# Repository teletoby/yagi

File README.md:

# yagi
Yet Another Geiger Instrument

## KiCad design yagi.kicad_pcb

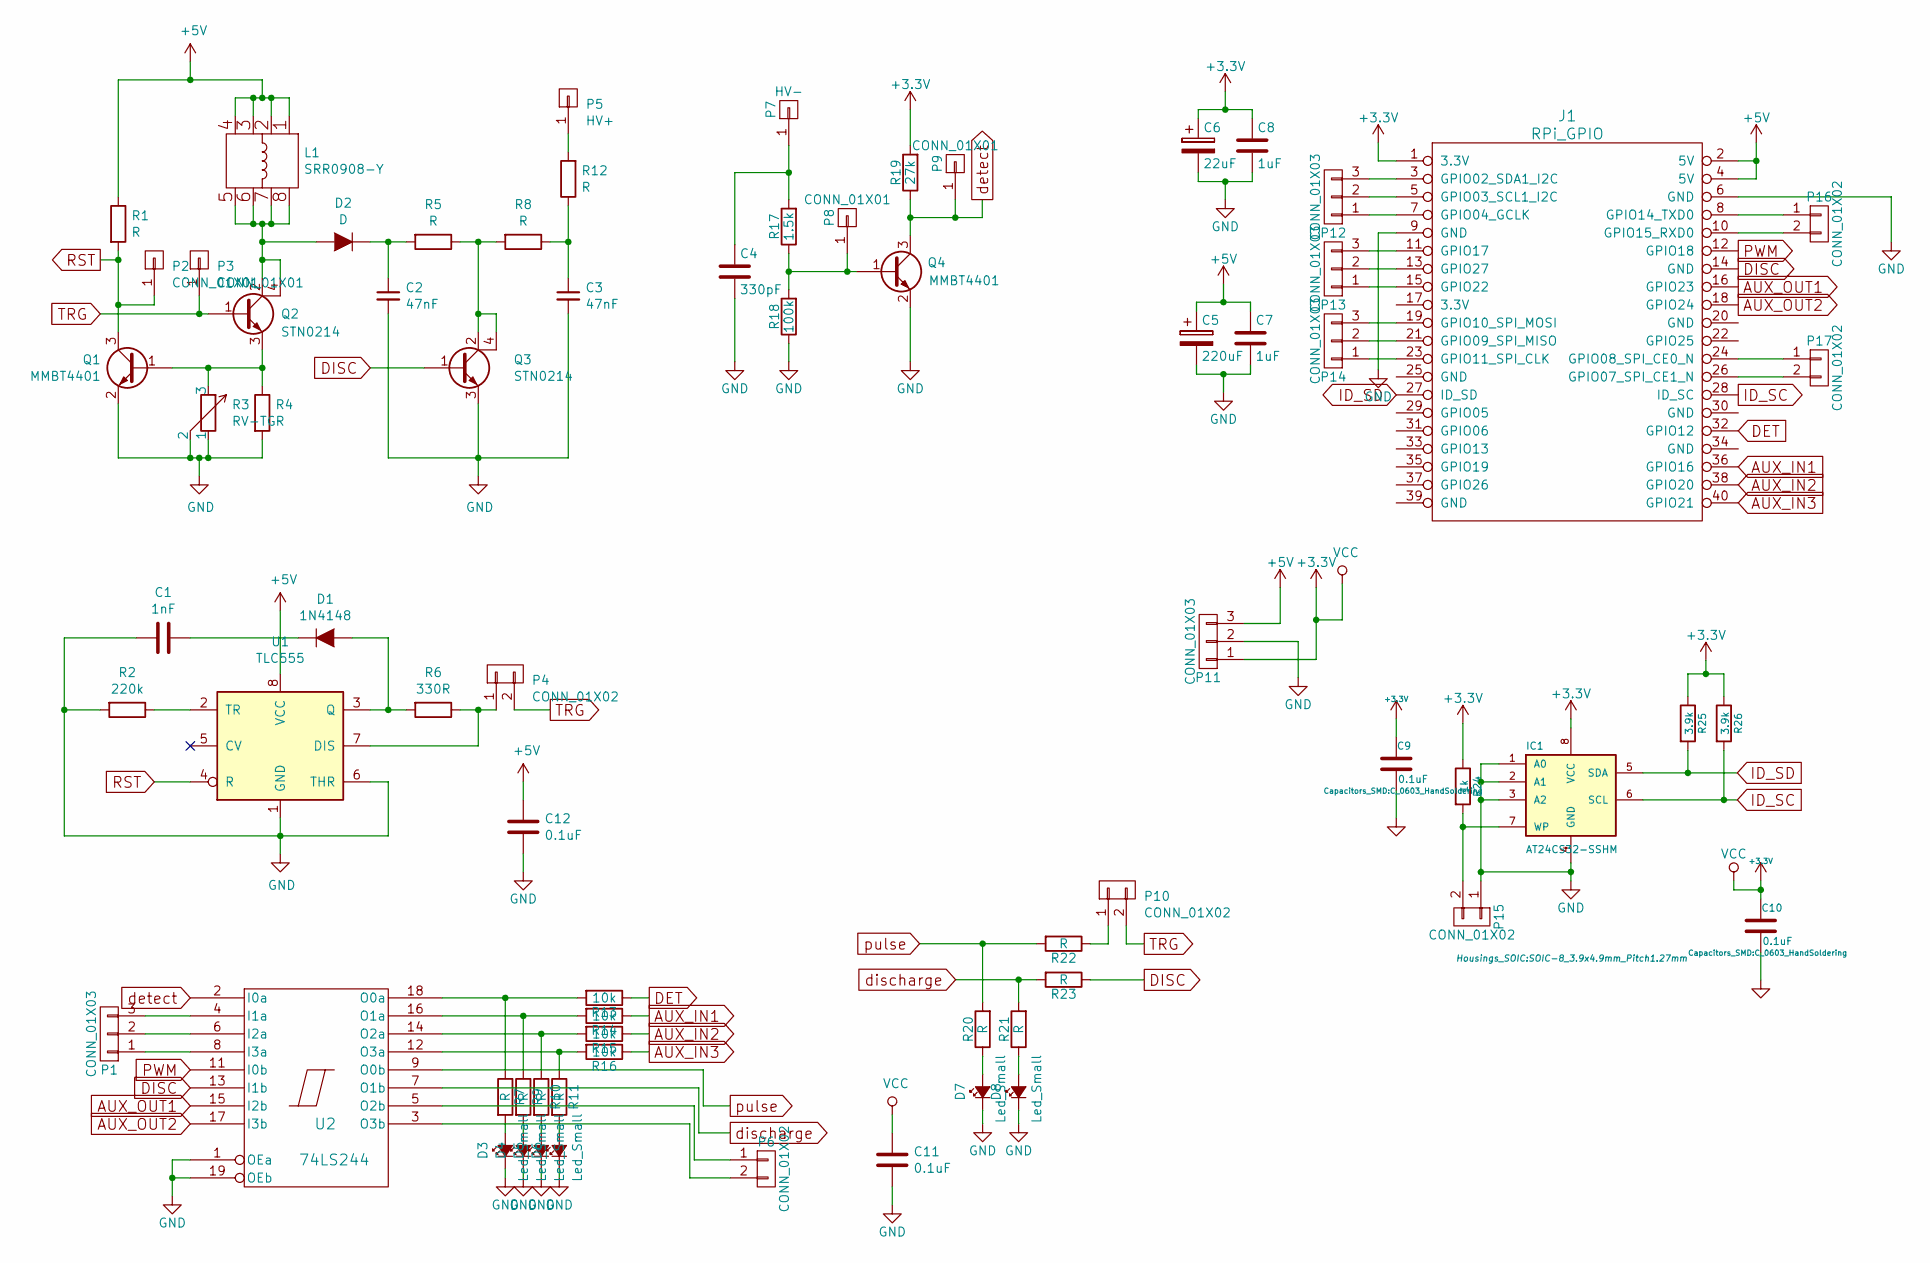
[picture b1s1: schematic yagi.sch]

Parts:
C1: 1nF; C_0805_HandSoldering
C2, C3: 47nF; C_1210_HandSoldering
C4: 330pF; C_0603_HandSoldering
C5: 220uF; c_elec_6.3x7.7
C6: 22uF; c_elec_5x4.5
C7, C8: 1uF; C_0805_HandSoldering
C9, C10, C11, C12: 0.1uF; C_0603_HandSoldering
D1: 1N4148; DO-35
D2: D; TUMD2SM
D3, D4, D5, D6, D7, D8: Led_Small; LED-0603
IC1: AT24CS32-SSHM; SOIC-8_3.9x4.9mm_Pitch1.27mm
J1: RPi_GPIO; Pin_Header_Straight_2x20
L1: SRR0908-Y
P1, P11, P12, P13, P14: CONN_01X03; Pin_Header_Straight_1x03
P2, P3: CONN_01X01; PIN
P4, P6, P10, P15, P16, P17: CONN_01X02; Pin_Header_Straight_1x02
P5: HV+; SolderWirePad_single_1-2mmDrill
P7: HV-; SolderWirePad_single_1-2mmDrill
P8, P9: CONN_01X01; SolderWirePad_single_0-8mmDrill
Q1, Q4: MMBT4401; SOT-23
Q2, Q3: STN0214; SOT-223
R1, R4, R5, R7, R8, R9, R10, R11, R12, R20, R21, R22, R23: R; R_0805_HandSoldering
R2: 220k; R_0805_HandSoldering
R3: RV-TG; bourns-3361-p
R6: 330R; R_0805_HandSoldering
R13, R14, R15, R16: 10k; R_0805_HandSoldering
R17: 1.5k; R_0805_HandSoldering
R18: 100k; R_0805_HandSoldering
R19: 27k; R_0805_HandSoldering
R24: 1k; R_0805_HandSoldering
R25, R26: 3.9k; R_0805_HandSoldering
U1: TLC555; SOIC-8_3.9x4.9mm_Pitch1.27mm
U2: 74LS244; TSSOP-20_4.4x6.5mm_Pitch0.65mm

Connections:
+3V3: C6.1, C8.1, C9.1, C10.1, C11.1, IC1.8 (VCC), J1.1 (3.3V), P11.1, R19.2, R24.1, R25.1, R26.1, U2.20 (VCC)
+5V: C5.1, C7.1, C12.1, J1.2 (5V), J1.4 (5V), L1.1, L1.2, L1.3, L1.4, P11.3, R1.1, U1.8 (VCC)
AUX_IN1: J1.36 (GPIO16), R14.1
AUX_IN2: J1.38 (GPIO20), R15.1
AUX_IN3: J1.40 (GPIO21), R16.1
AUX_OUT1: J1.16 (GPIO23), U2.15 (I2b)
AUX_OUT2: J1.18 (GPIO24), U2.17 (I3b)
DET: J1.32 (GPIO12), R13.1
DISC: J1.14 (GND), Q3.1 (B), U2.13 (I1b)
GND: C1.2, C2.2, C3.2, C4.2, C5.2, C6.2, C7.2, C8.2, C9.2, C10.2, C11.2, C12.2, D3.1 (K), D4.1 (K), D5.1 (K), D6.1 (K), D7.1 (K), D8.1 (K), IC1.1 (A0), IC1.2 (A1), IC1.3 (A2), IC1.4 (GND), J1.6 (GND), J1.9 (GND), P11.2, P15.1, Q1.2 (E), Q3.3 (E), Q4.2 (E), R2.2, R3.1, R3.2, R4.2, R18.1, U1.1 (GND), U1.6 (THR), U2.1 (OEa), U2.10 (GND), U2.19 (OEb)
ID_SC: IC1.6 (SCL), J1.28 (ID_SC), R26.2
ID_SD: IC1.5 (SDA), J1.27 (ID_SD), R25.2
unnamed: C1.1, D1.1 (K)
unnamed: C2.1, D2.1 (K), R5.2
unnamed: C3.1, R8.1, R12.1
unnamed: C4.1, P7.1, R17.2
unnamed: D1.2 (A), R6.2, U1.3 (Q)
unnamed: D2.2 (A), L1.5, L1.6, L1.7, L1.8, Q2.2 (C), Q2.4 (C)
unnamed: D3.2 (A), R7.2
unnamed: D4.2 (A), R9.2
unnamed: D5.2 (A), R10.2
unnamed: D6.2 (A), R11.2
unnamed: D7.2 (A), R20.1
unnamed: D8.2 (A), R21.1
unnamed: IC1.7 (WP), P15.2, R24.2
unnamed: J1.3 (GPIO02_SDA1_I2C), P12.3
unnamed: J1.5 (GPIO03_SCL1_I2C), P12.2
unnamed: J1.7 (GPIO04_GCLK), P12.1
unnamed: J1.8 (GPIO14_TXD0), P16.1
unnamed: J1.10 (GPIO15_RXD0), P16.2
unnamed: J1.11 (GPIO17), P13.3
unnamed: J1.13 (GPIO27), P13.2
unnamed: J1.15 (GPIO22), P13.1
unnamed: J1.19 (GPIO10_SPI_MOSI), P14.3
unnamed: J1.21 (GPIO09_SPI_MISO), P14.2
unnamed: J1.23 (GPIO11_SPI_CLK), P14.1
unnamed: J1.24 (GPIO08_SPI_CE0_N), P17.1
unnamed: J1.26 (GPIO07_SPI_CE1_N), P17.2
unnamed: P1.1, U2.8 (I3a)
unnamed: P1.2, U2.6 (I2a)
unnamed: P1.3, U2.4 (I1a)
unnamed: P4.1, R6.1, U1.7 (DIS)
unnamed: P5.1, R12.2
unnamed: P6.1, U2.5 (O2b)
unnamed: P6.2, U2.3 (O3b)
unnamed: P8.1, Q4.1 (B), R17.1, R18.2
unnamed: Q1.1 (B), Q2.3 (E), R3.3, R4.1
unnamed: Q3.2 (C), Q3.4 (C), R5.1, R8.2
unnamed: R2.1, U1.2 (TR)
unnamed: R10.1, R15.2, U2.14 (O2a)
unnamed: R11.1, R16.2, U2.12 (O3a)
unnamed: R7.1, R13.2, U2.18 (O0a)
unnamed: R9.1, R14.2, U2.16 (O1a)
PWM: J1.12 (GPIO18), U2.11 (I0b)
RST: P2.1, Q1.3 (C), R1.2, U1.4 (R)
TRG: P3.1, P4.2, P10.2, Q2.1 (B)
detect: P9.1, Q4.3 (C), R19.1, U2.2 (I0a)
discharge: R21.2, R23.2, U2.7 (O1b)
pulse: R20.2, R22.2, U2.9 (O0b)

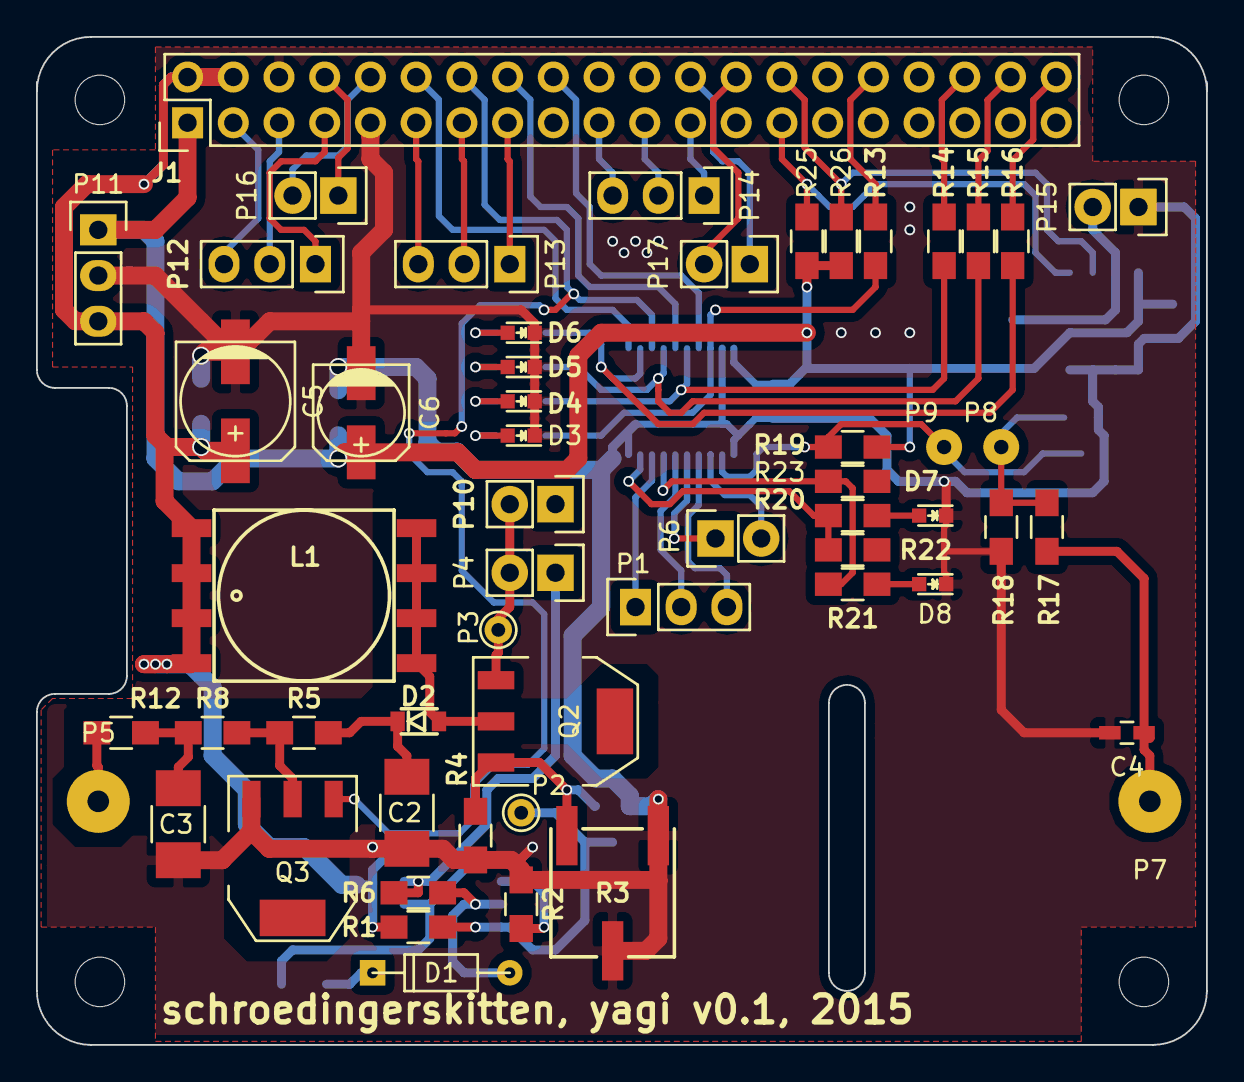
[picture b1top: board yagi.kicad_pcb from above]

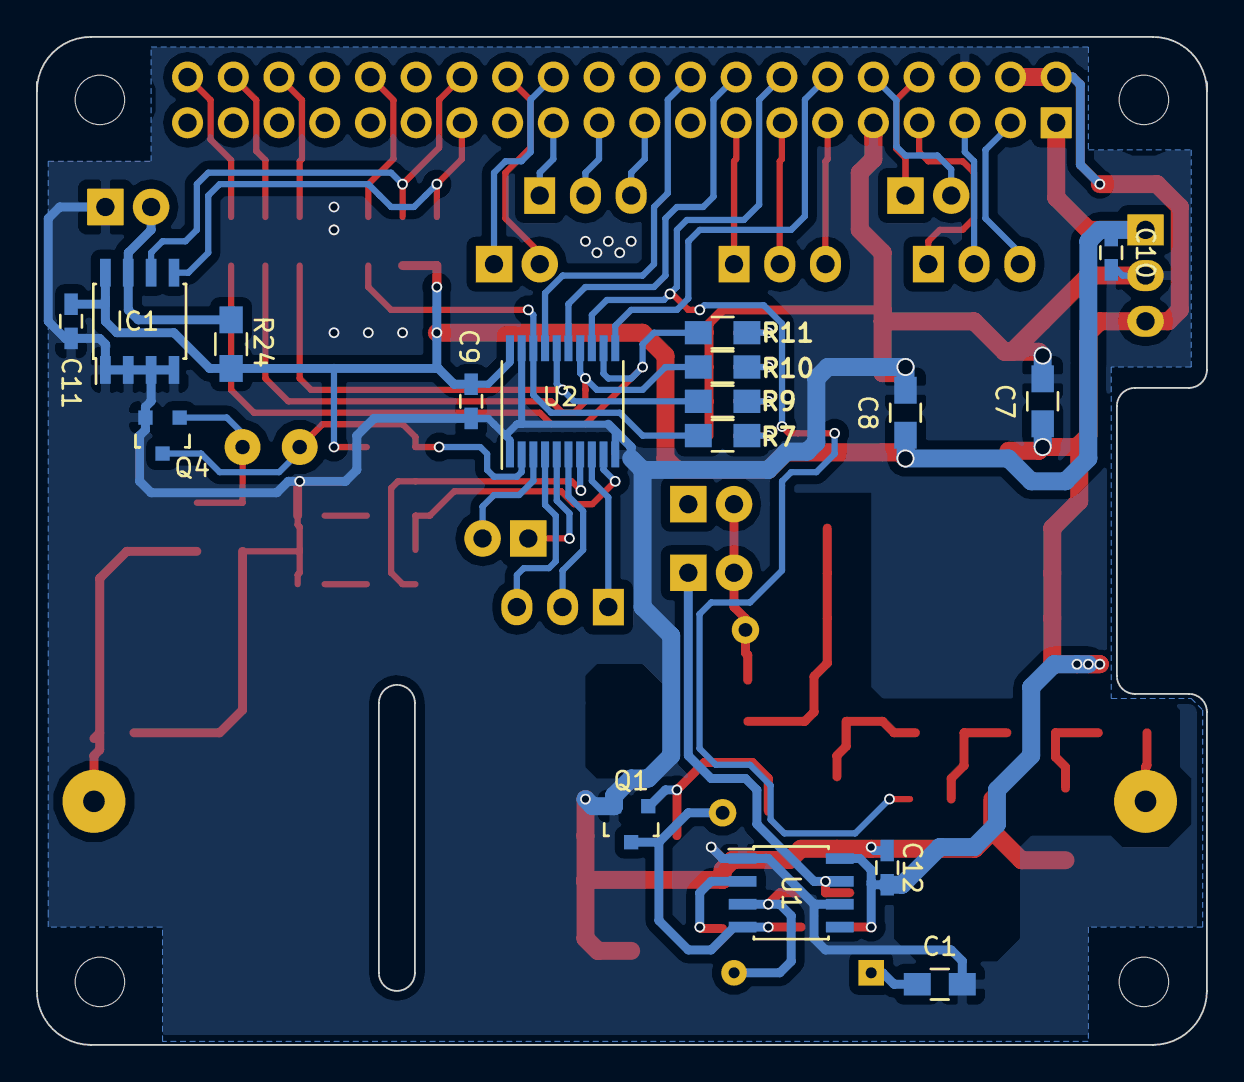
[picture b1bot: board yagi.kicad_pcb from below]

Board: 2 copper layers, 65.0 x 56.0 mm, 72 parts (17 on the bottom side), 59 nets.

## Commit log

2015-09-25 Add early draft
2015-10-01 Layouting
2015-10-03 Finish layouting.
2015-10-03 Add pins for easy current measurement for coil.
2016-01-03 New try.
2016-01-03 Renamed files according to seeed guidelines.
